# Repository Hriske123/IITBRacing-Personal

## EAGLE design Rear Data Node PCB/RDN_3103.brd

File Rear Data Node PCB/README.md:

This board reads the output of the rear sensors strain gauge, loadcell and rear suspensions

Version Information/ Reviews: https://docs.google.com/document/d/1en4HirWPAX3mzluUavpXsB_PTmQg_GlgoAHJ7ktcT14/edit?tab=t.0

Documentation: https://docs.google.com/document/d/10uqbX0Noolaf0F8rlXxzqJK7N5m3tU4yje-vPbJN5Zs/edit?tab=t.0

INA 333 testing data: https://docs.google.com/spreadsheets/d/1m1x5NLFQ7lGrNK6-yPvDKJtSeQUF5GOdyU59EFBAQz0/edit?usp=sharing

INA 122U testing data: https://docs.google.com/spreadsheets/d/1WMfO3j6cnKqHVtRB1KXYtjKCPefr-8N02gxwBF3gpQY/edit?usp=sharing

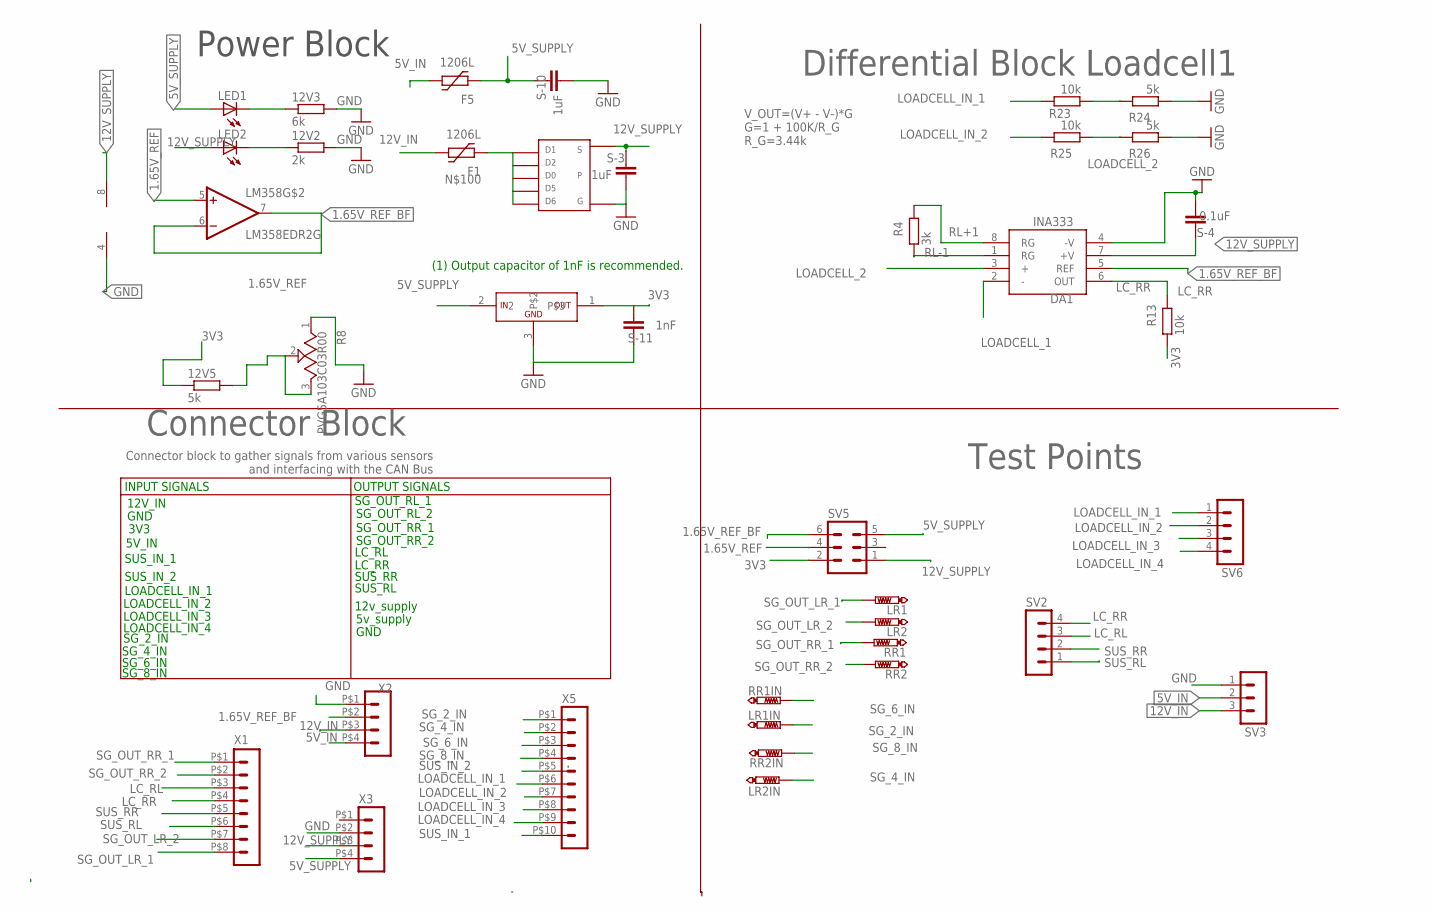
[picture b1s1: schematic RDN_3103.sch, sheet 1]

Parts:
12V2: 2k; R0805
12V3: 6k; R0805
12V5: 5k; R0805
DA1: INA333; MSOP8
F1, F5: 1206L
LED1, LED2: LEDCHIPLED_1206; CHIPLED_1206
LM358: LM358EDR2G; SOIC-8
LR1, LR1IN, LR2, LR2IN: PTR1PAD1-13; P1-13
R4: 3k; R0805
R8: PVG5A103C03R00; TRIM_PVG5A103C03R00
R13, R23, R25: 10k; R0805
R24, R26: 5k; R0805
RR1, RR1IN, RR2, RR2IN: PTR1PAD1-13; P1-13
S-3, S-10: 1uF; C0805
S-4: 0.1uF; C0805
S-11: 1nF; C0805
SV2, SV6: MA04-1
SV3: MA03-1
SV5: MA03-2
U$1: TSOP-6_PMOS
U$3: 3V3_REGULATOR; SOT-23
X1: HEADER_POS8_43045-0800; 43045-0800
X2, X3: HEADER_POS4_43045-0401; 43045-0400
X5: HEADER_POS10_43045-1000; 43045-1000

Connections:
1.65V_REF: 12V5.2, LM358.5 (+IN), R8.2, R8.3, SV5.4
1.65V_REF_BF: DA1.5 (REF), LM358.6 (-IN), LM358.7 (OUT), SV5.6, X2.P$2 (2); also elsewhere on the board
3V3: 12V5.1, R13.1, S-11.2, SV5.2, U$3.1; also elsewhere on the board
5V_IN: F5.P$2 (2), SV3.2, X2.P$4 (4)
5V_SUPPLY: F5.P$1 (1), LED1.A, S-10.1, SV5.5, U$3.2, X3.P$4 (4); also elsewhere on the board
12V_IN: F1.P$2 (2), SV3.3, X2.P$3 (3)
12V_SUPPLY: DA1.7 (+V), LED2.A, LM358.8 (V+), S-3.1, S-4.1, SV5.1, U$1.S, X3.P$3 (3); also elsewhere on the board
GND: 12V2.2, 12V3.2, DA1.4 (-V), LM358.4 (V-), R8.1, R24.1, R26.1, S-3.2, S-4.2, S-10.2, S-11.1, SV3.1, U$1.G, U$3.3, X2.P$1 (1), X3.P$2 (2); also elsewhere on the board
LC_RL: SV2.3, X1.P$3 (3); also elsewhere on the board
LC_RR: DA1.6 (OUT), R13.2, SV2.4, X1.P$4 (4)
LOADCELL_1: DA1.2 (-), R23.1, R24.2
LOADCELL_2: DA1.3 (+), R25.1, R26.2
LOADCELL_IN_1: R23.2, SV6.1, X5.P$6 (6)
LOADCELL_IN_2: R25.2, SV6.2, X5.P$7 (7)
LOADCELL_IN_3: SV6.3, X5.P$8 (8); also elsewhere on the board
LOADCELL_IN_4: SV6.4, X5.P$9 (9); also elsewhere on the board
unnamed: 12V2.1, LED2.C
unnamed: 12V3.1, LED1.C
unnamed: F1.P$1 (1), U$1.1, U$1.2, U$1.5, U$1.6, U$1.D (D0)
RL+1: DA1.8 (RG), R4.2
RL-1: DA1.1 (RG), R4.1
SG_2_IN: LR1IN.TP, X5.P$1 (1); also elsewhere on the board
SG_4_IN: LR2IN.TP, X5.P$2 (2); also elsewhere on the board
SG_6_IN: RR1IN.TP, X5.P$3 (3); also elsewhere on the board
SG_8_IN: RR2IN.TP, X5.P$4 (4); also elsewhere on the board
SG_OUT_LR_1: LR1.TP, X1.P$8 (8); also elsewhere on the board
SG_OUT_LR_2: LR2.TP, X1.P$7 (7); also elsewhere on the board
SG_OUT_RR_1: RR1.TP, X1.P$1 (1); also elsewhere on the board
SG_OUT_RR_2: RR2.TP, X1.P$2 (2); also elsewhere on the board
SUS_IN_1: X5.P$10 (10); also elsewhere on the board
SUS_IN_2: X5.P$5 (5); also elsewhere on the board
SUS_RL: SV2.1, X1.P$6 (6); also elsewhere on the board
SUS_RR: SV2.2, X1.P$5 (5); also elsewhere on the board

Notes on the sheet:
Connector Block
Power Block
Connector block to gather signals from various sensors and interfacing with the CAN Bus
Differential Block Loadcell1
Test Points
INPUT SIGNALS
12V_IN
GND
3V3
5V_IN
SUS_IN_1
SUS_IN_2
LOADCELL_IN_1
LOADCELL_IN_2
LOADCELL_IN_3
LOADCELL_IN_4
SG_2_IN
SG_4_IN
SG_6_IN
SG_8_IN
OUTPUT SIGNALS
SG_OUT_RL_1
SG_OUT_RL_2
SG_OUT_RR_1
SG_OUT_RR_2
LC_RL
LC_RR
SUS_RR
SUS_RL
12v_supply
5v_supply
V_OUT=(V+ - V-)*G G=1 + 100K/R_G R_G=3.44k
(1) Output capacitor of 1nF is recommended.

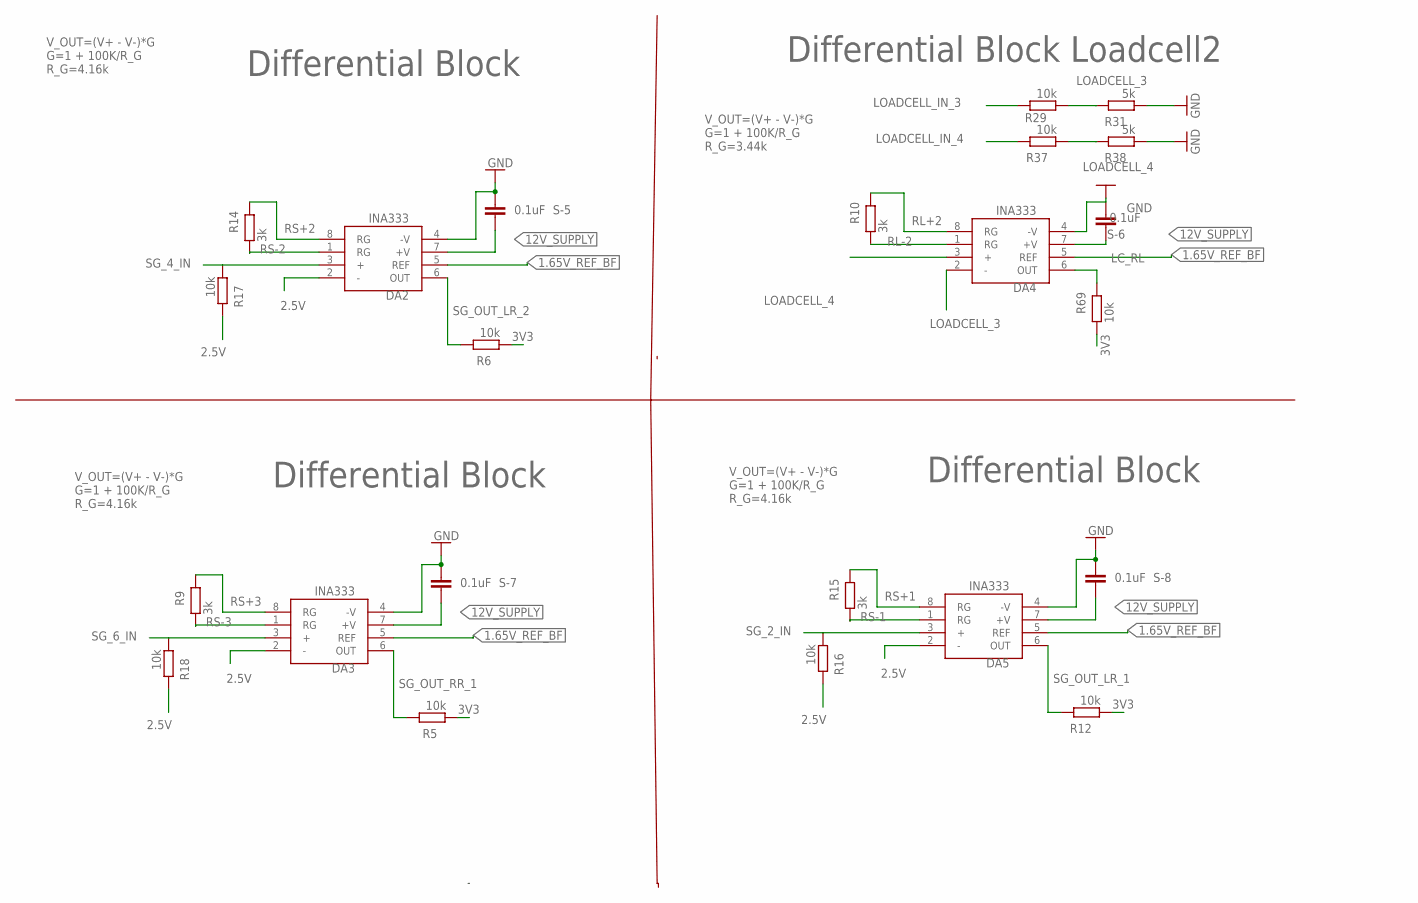
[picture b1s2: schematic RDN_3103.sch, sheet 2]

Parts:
DA2, DA3, DA4, DA5: INA333; MSOP8
R5, R6, R12, R16, R17, R18, R29, R37, R69: 10k; R0805
R9, R10, R14, R15: 3k; R0805
R31, R38: 5k; R0805
S-5, S-6, S-7, S-8: 0.1uF; C0805

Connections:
1.65V_REF_BF: DA2.5 (REF), DA3.5 (REF), DA4.5 (REF), DA5.5 (REF); also elsewhere on the board
2.5V: DA2.2 (-), DA3.2 (-), DA5.2 (-), R16.2, R17.2, R18.2; also elsewhere on the board
3V3: R5.1, R6.1, R12.1, R69.1; also elsewhere on the board
12V_SUPPLY: DA2.7 (+V), DA3.7 (+V), DA4.7 (+V), DA5.7 (+V), S-5.1, S-6.1, S-7.1, S-8.1; also elsewhere on the board
GND: DA2.4 (-V), DA3.4 (-V), DA4.4 (-V), DA5.4 (-V), R31.1, R38.1, S-5.2, S-6.2, S-7.2, S-8.2; also elsewhere on the board
LC_RL: DA4.6 (OUT), R69.2; also elsewhere on the board
LOADCELL_3: DA4.2 (-), R29.1, R31.2
LOADCELL_4: DA4.3 (+), R37.1, R38.2
LOADCELL_IN_3: R29.2; also elsewhere on the board
LOADCELL_IN_4: R37.2; also elsewhere on the board
RL+2: DA4.8 (RG), R10.2
RL-2: DA4.1 (RG), R10.1
RS+1: DA5.8 (RG), R15.2
RS+2: DA2.8 (RG), R14.2
RS+3: DA3.8 (RG), R9.2
RS-1: DA5.1 (RG), R15.1
RS-2: DA2.1 (RG), R14.1
RS-3: DA3.1 (RG), R9.1
SG_2_IN: DA5.3 (+), R16.1; also elsewhere on the board
SG_4_IN: DA2.3 (+), R17.1; also elsewhere on the board
SG_6_IN: DA3.3 (+), R18.1; also elsewhere on the board
SG_OUT_LR_1: DA5.6 (OUT), R12.2; also elsewhere on the board
SG_OUT_LR_2: DA2.6 (OUT), R6.2; also elsewhere on the board
SG_OUT_RR_1: DA3.6 (OUT), R5.2; also elsewhere on the board

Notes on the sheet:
Differential Block Loadcell2
Differential Block
V_OUT=(V+ - V-)*G G=1 + 100K/R_G R_G=4.16k
V_OUT=(V+ - V-)*G G=1 + 100K/R_G R_G=3.44k

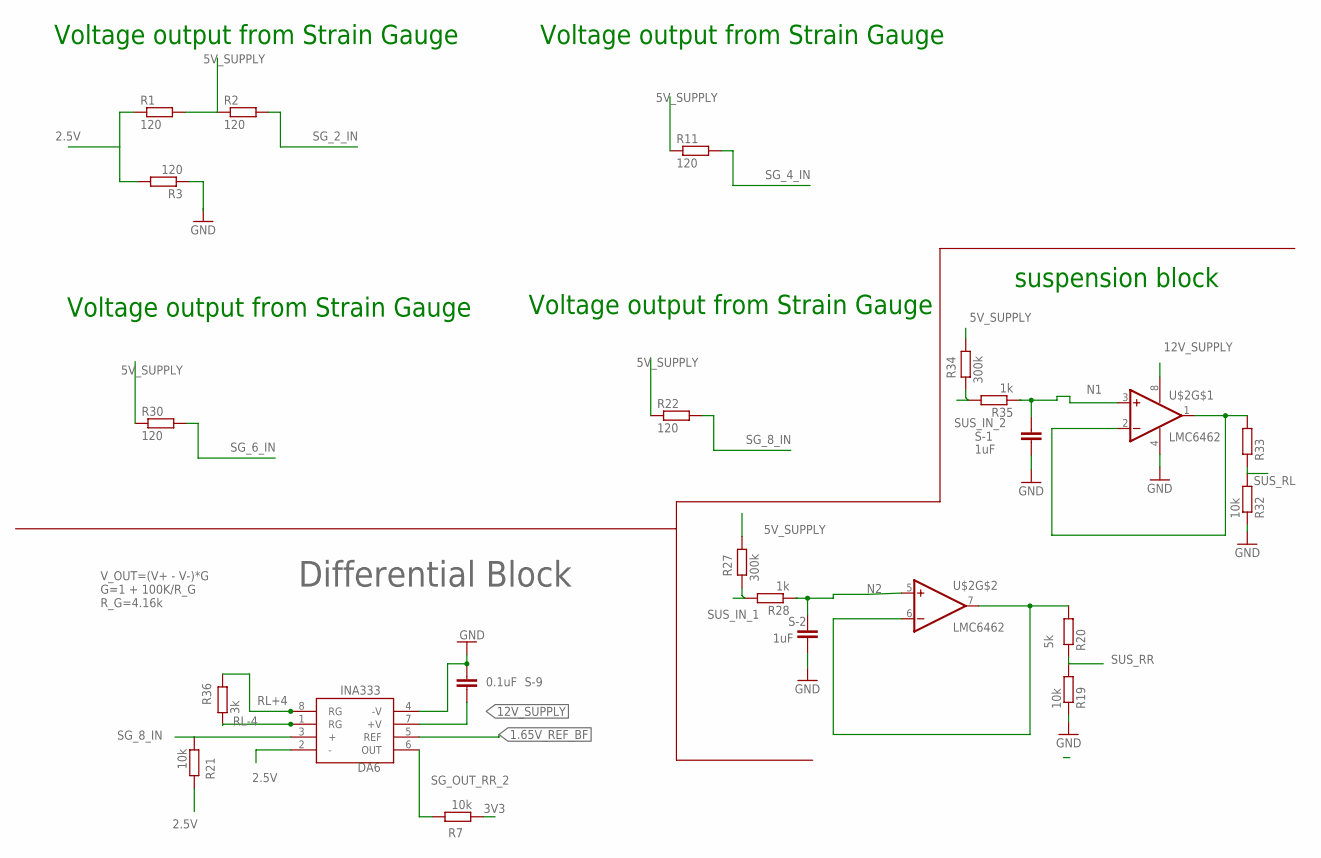
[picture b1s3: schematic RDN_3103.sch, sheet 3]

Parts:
DA6: INA333; MSOP8
R1, R2, R3, R11, R22, R30: 120; R0805
R7, R19, R21, R32: 10k; R0805
R20, R33: 5k; R0805
R27, R34: 300k; R0805
R28, R35: 1k; R0805
R36: 3k; R0805
S-1, S-2: 1uF; C0805
S-9: 0.1uF; C0805
U$2: LMC6462; S08

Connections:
1.65V_REF_BF: DA6.5 (REF); also elsewhere on the board
2.5V: DA6.2 (-), R1.1, R3.2, R21.2; also elsewhere on the board
3V3: R7.1; also elsewhere on the board
5V_SUPPLY: R1.2, R2.1, R11.1, R22.1, R27.2, R30.1, R34.2; also elsewhere on the board
12V_SUPPLY: DA6.7 (+V), S-9.1, U$2.8 (V+); also elsewhere on the board
GND: DA6.4 (-V), R3.1, R19.1, R32.1, S-1.2, S-2.2, S-9.2, U$2.4 (V-); also elsewhere on the board
N1: R35.1, S-1.1, U$2.3 (+IN)
N2: R28.1, S-2.1, U$2.5 (+IN)
unnamed: R20.2, U$2.6 (-IN), U$2.7 (OUT)
unnamed: R33.2, U$2.1 (OUT), U$2.2 (-IN)
RL+4: DA6.8 (RG), R36.2
RL-4: DA6.1 (RG), R36.1
SG_2_IN: R2.2; also elsewhere on the board
SG_4_IN: R11.2; also elsewhere on the board
SG_6_IN: R30.2; also elsewhere on the board
SG_8_IN: DA6.3 (+), R21.1, R22.2; also elsewhere on the board
SG_OUT_RR_2: DA6.6 (OUT), R7.2; also elsewhere on the board
SUS_IN_1: R27.1, R28.2; also elsewhere on the board
SUS_IN_2: R34.1, R35.2; also elsewhere on the board
SUS_RL: R32.2, R33.1; also elsewhere on the board
SUS_RR: R19.2, R20.1; also elsewhere on the board

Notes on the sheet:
Voltage output from Strain Gauge
suspension block
Differential Block
V_OUT=(V+ - V-)*G G=1 + 100K/R_G R_G=4.16k

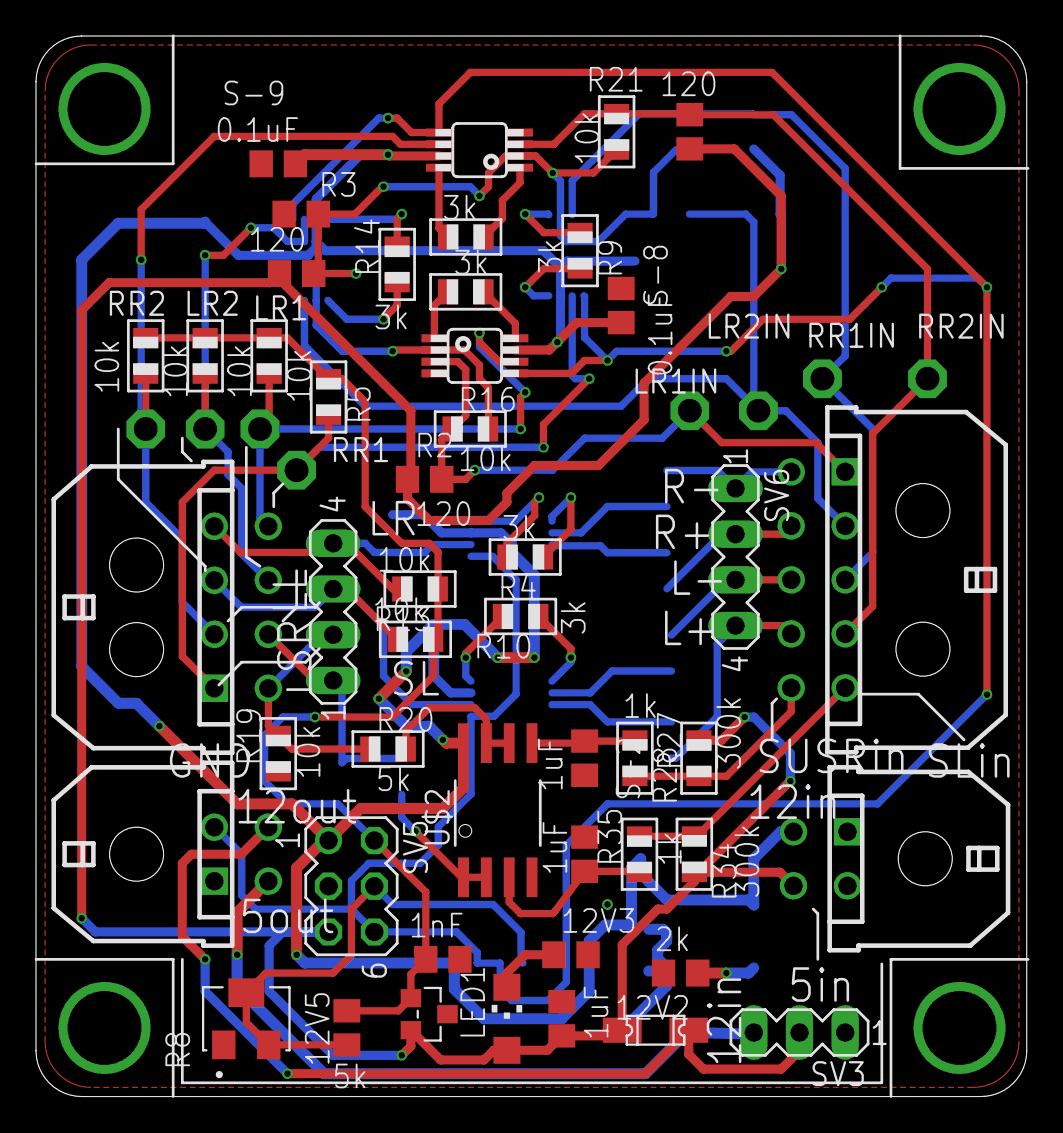
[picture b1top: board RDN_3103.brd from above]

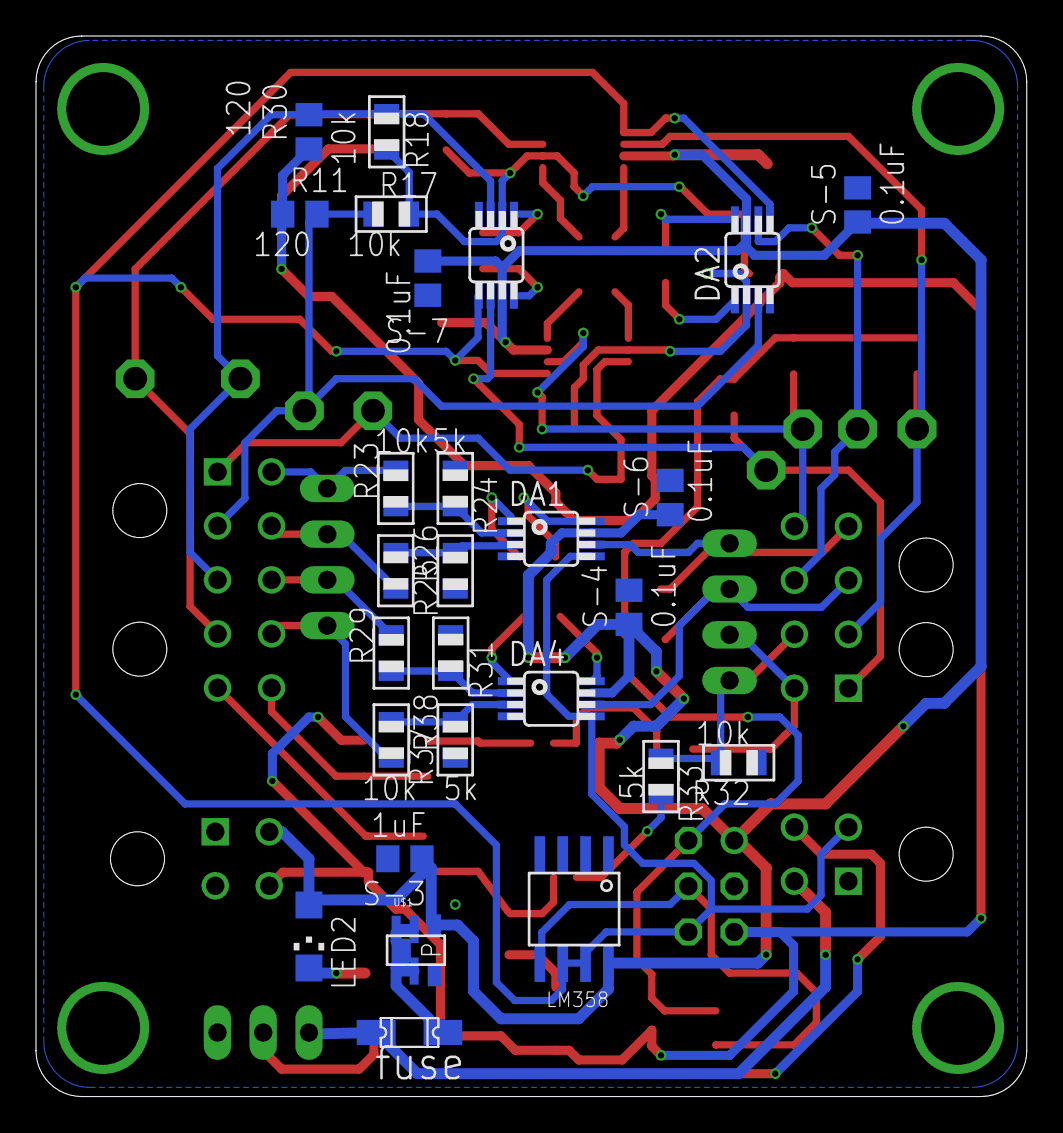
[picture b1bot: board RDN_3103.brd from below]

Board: 2 copper layers, 55.0 x 58.9 mm, 83 parts (27 on the bottom side), 50 nets.

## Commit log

2025-09-25 Create Test
